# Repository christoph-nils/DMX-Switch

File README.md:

# DMX-Switch

[Hier ist das Projekt inklusive Bilder](http://christoph-nils.de/elektronik/dmx-switch/) bzw. [hier](http://data.christoph-nils.de/diverses/DMX-Switch.zip)  
Ein simpler DMX-Switch für die Hutschiene. Zur Adressierung wird ein Taster gedrückt und speichert die erste Adresse mit DMX-Wert > 128 als Startadresse.  
Ein Kanal kann auch zur Signalisierung eines gültigen DMX-Signals verwendet werden.  
Der Source-Code basiert auf diesem [Code](https://www.mikrocontroller.net/topic/185804)  
Lizenz: http://creativecommons.org/licenses/by-nc/3.0/de/

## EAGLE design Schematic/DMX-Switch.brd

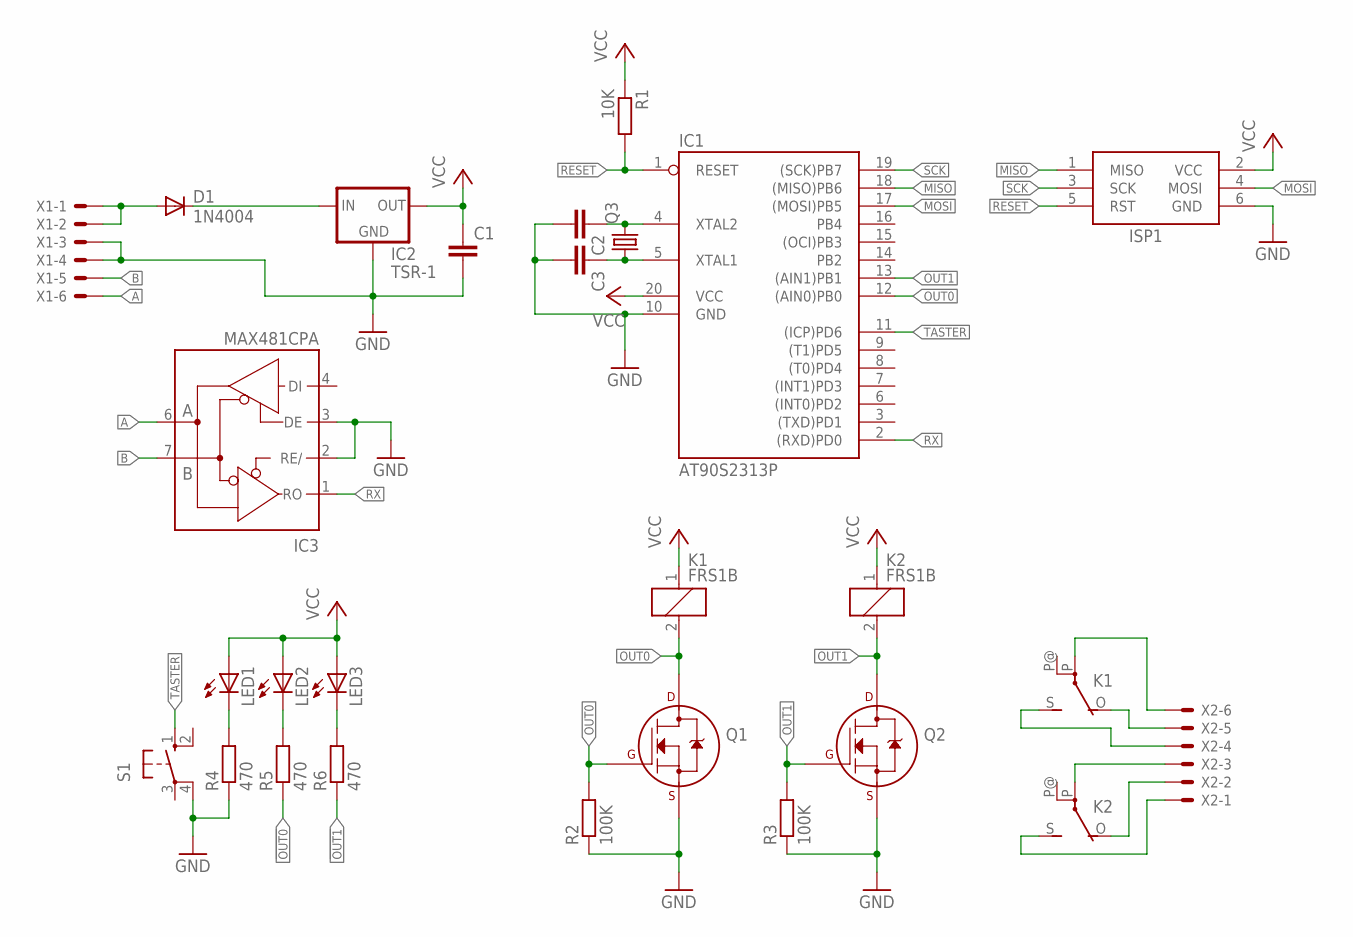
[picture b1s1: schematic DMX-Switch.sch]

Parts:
C1, C2, C3: C-EU025-024X044; C025-024X044
D1: 1N4004; DO41-10
IC1: AT90S2313P; DIL20
IC2: TSR-1
IC3: MAX481CPA; DIL08
ISP1: AVRISP-BOX
K1, K2: FRS1B
LED1, LED2, LED3: LED5MM
Q1, Q2: 2N7000_TO92; TO-92
Q3: CRYSTALHC49S; HC49/S
R1: 10K; 0204/7
R2, R3: 100K; 0204/7
R4, R5, R6: 470; 0204/7
S1: 10-XX; B3F-10XX
X1, X2: KK-156-6

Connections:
!OUT0: K1.2, Q1.3 (D), R5.1
!OUT1: K2.2, Q2.3 (D), R6.1
A: IC3.6 (A), X1.6
B: IC3.7 (B), X1.5
GND: C1.2, C2.2, C3.2, IC1.10 (GND), IC2.2 (GND), IC3.2 (RE/), IC3.3 (DE), IC3.5 (GND), ISP1.6 (GND), Q1.1 (S), Q2.1 (S), R2.1, R3.1, R4.1, S1.4 (P1), X1.3, X1.4
MISO: IC1.18 ((MISO)PB6), ISP1.1 (MISO)
MOSI: IC1.17 ((MOSI)PB5), ISP1.4 (MOSI)
unnamed: D1.A, X1.1, X1.2
unnamed: D1.C, IC2.1 (IN)
unnamed: C3.1, IC1.5 (XTAL1), Q3.1
unnamed: C2.1, IC1.4 (XTAL2), Q3.2
unnamed: LED1.K (C), R4.2
unnamed: LED2.K (C), R5.2
unnamed: LED3.K (C), R6.2
unnamed: K1.S, X2.4
unnamed: K1.O, X2.5
unnamed: K1.P, X2.6
unnamed: K2.P, X2.3
unnamed: K2.O, X2.2
unnamed: K2.S, X2.1
OUT0: IC1.12 ((AIN0)PB0), Q1.2 (G), R2.2
OUT1: IC1.13 ((AIN1)PB1), Q2.2 (G), R3.2
RESET: IC1.1 (RESET), ISP1.5 (RST), R1.2
RX: IC1.2 ((RXD)PD0), IC3.1 (RO)
SCK: IC1.19 ((SCK)PB7), ISP1.3 (SCK)
TASTER: IC1.11 ((ICP)PD6), S1.1 (S)
VCC: C1.1, IC1.20 (VCC), IC2.3 (OUT), IC3.8 (VCC), ISP1.2 (VCC), K1.1, K2.1, LED1.A, LED2.A, LED3.A, R1.1

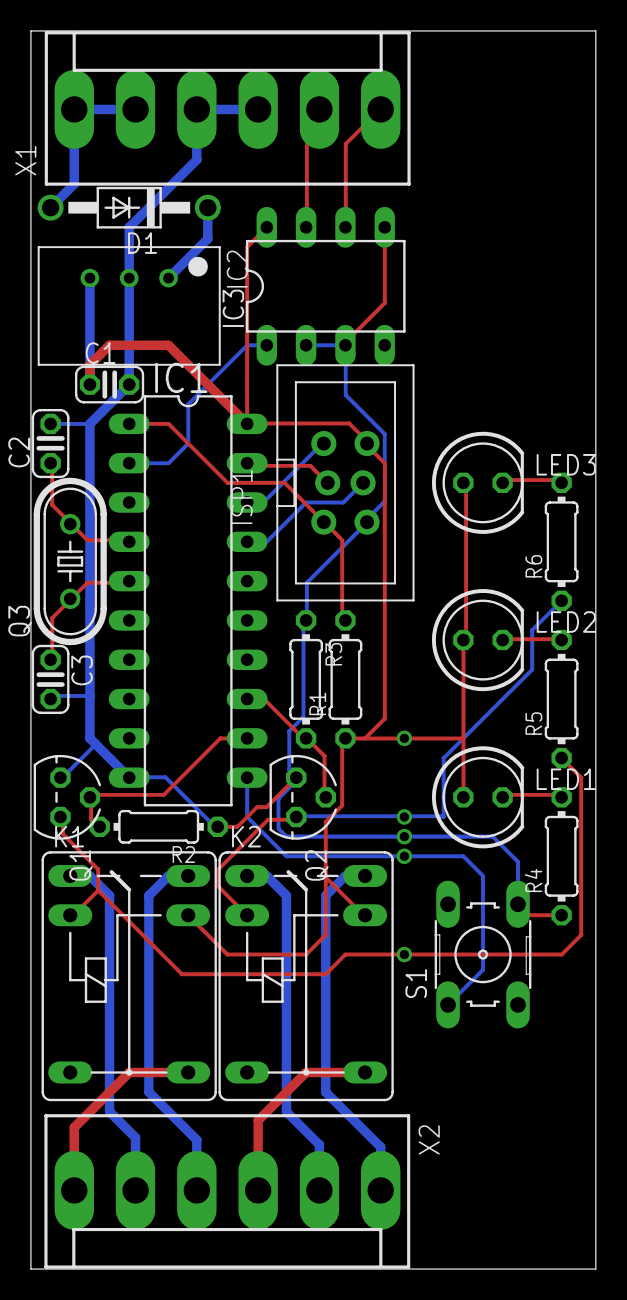
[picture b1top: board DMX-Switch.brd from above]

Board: 2 copper layers, 36.5 x 80.0 mm, 25 parts (0 on the bottom side), 27 nets.

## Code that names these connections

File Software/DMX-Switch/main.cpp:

/**

 * Original https://www.mikrocontroller.net/topic/185804
 * Editiert von Christoph Nils Schäfer <mail@christoph-nils.de>
 * DMX Switch zur Signalisierung der DMX Verfügbarkeit
 * und ein per DMX schaltbarer Kanal
 * Startadresse per Taster und DMX einstellbar

 * DMX Receiver 
 * 2*8bit linear pwm, 2*16bit exponential pwm
 *
 * @author Andi Dittrich <andi.dittrich@a3non.org>
 * @website http://www.a3non.org
 * @modified 31.07.2010
 * @license CC BY-NC
 * @license http://creativecommons.org/licenses/by-nc/3.0/de/
 * @target AtTiny2313
 * @cpu 16MHz
*/
#define F_CPU 16000000UL

#include <avr/interrupt.h>
#include <stdio.h>
#include <inttypes.h>
#include <avr/io.h>
#include <avr/pgmspace.h>
#include <avr/wdt.h>
#include <util/delay.h>
#include <avr/eeprom.h>
#include "mydefs.h"

// number of receiving channels
#define DMX_CHANNELS 1

//PD0	RX
//PD6	Taster Set-CH-n
//PB0	Relais DMX-OK
//PB1	Relais DMX-CH-n

#define	RX_PORT			SBIT( PORTD, 0 )
#define	RX_DDR			SBIT( DDRD,  0 )
#define	Taster_PORT		SBIT( PORTD, 6 )
#define	Taster_PIN		SBIT( PIND,  6 )
#define	Taster_DDR		SBIT( DDRD,  6 )
#define	Relais_0_OUT	SBIT( PORTB, 0 )
#define	Relais_0_DDR	SBIT( DDRB,  0 )
#define	Relais_1_OUT	SBIT( PORTB, 1 )
#define	Relais_1_DDR	SBIT( DDRB,  1 )

// DMX address
volatile uint16_t DMXAddress = 1;

// dmx storage array
volatile uint8_t dmx_data[DMX_CHANNELS];

// dmx states
enum {IDLE = 0, BREAK, READ, SETADDRESS};

// actual dmx state
volatile uint8_t DMXState = IDLE;

// valid sequence
volatile uint8_t VALID_DATA = 0;

// channel input read count
volatile uint16_t DMXFrameCount = 0;


// MAIN
int main(){
	// disable ISR
	cli();
	
	RX_DDR = 0;
	RX_PORT = 0;
	Taster_DDR = 0;
	Taster_PORT = 1;
	Relais_0_OUT = 0;
	Relais_0_DDR = 1;
	Relais_1_OUT = 0;
	Relais_1_DDR = 1;

	// 250k baud - 16MHz - U2X=0
	UBRRL = 3;
	UBRRH = 0;
	
	
	// UART CONTROL
	// 7:0 - RXC - USART Receive Complete
	// 6:0 - TXC - USART Transmit Complete
	// 5:0 - UDRE - USART Data Register Empty
	// 4:0 - FE - Frame Error
	// 3:0 - DOR - Data OverRun
	// 2:0 - UPE - USART Parity Error
	// 1:0 - U2X - Double the USART Transmission Speed
	// 0:0 - MPCM - Multi-processor Communication Mode
	UCSRA = 0b00000000;
	
	// 7:0 - reserved
	// 6:0 - UMSEL - async operation
	// 5:0 - UPM1 - no paritiy
	// 4:0 - UPM0 - no paritiy
	// 3:1 - USBS - 2 stop bits
	// 2:1 - UCSZ1 - 8bit mode
	// 1:1 - UCSZ0 - 8bit mode
	// 0:0 - UCPOL - clock polarity, rising edge
	UCSRC = 0b00001110;

	// UART CONTROL
	// 7:1 - RXCIE - RX Complete Interrupt Enable
	// 6:0 - TXCIE - TX Complete Interrupt Disable
	// 5:0 - UDRIE - USART Data Register Empty Interrupt Disable
	// 4:1 - RXEN - Receiver Enable
	// 3:0 - TXEN - Transmitter Disable
	// 2:0 - UCSZ2 - 8bit mode
	// 1:0 - RXB8 - Receive Data Bit 8
	// 0:0 - TXB8 - Transmit Data Bit 8
	UCSRB = 0b10010000;

	// WATCHDOG - 4s
	// 7:0 - Watchdog Interrupt Flag
	// 6:1 - Watchdog Interrupt Enable
	// 5:1 - Watchdog Timer Prescaler3
	// 4:1 - Watchdog Change Enable
	// 3:0 - Watchdog System Reset Disable
	// 2:0 - Watchdog Timer Prescaler2
	// 1:0 - Watchdog Timer Prescaler1
	// 0:0 - Watchdog Timer Prescaler0
	WDTCR = 0b01110000;	

	// reset watchdog
	MCUSR &= ~(1<<WDRF);
			
	// initialize DMX State
	DMXState = IDLE;

	// initialize data array
	for (uint8_t i=0;i<DMX_CHANNELS;i++){
		dmx_data[i]= 0;
	}

	//Load DMX Address
	DMXAddress = eeprom_read_word(0);

	// enable dmx rx
	sei();

	// main loop
	while (true){
		// assign channels
		if (VALID_DATA){
			// on valid frame, assign values to ouputs
			
			if(dmx_data[0]>=128)
				Relais_1_OUT = 1;
			else
				Relais_1_OUT = 0;
			Relais_0_OUT = 1; //DMX OK
		}else{
			// deactivate all outputs on dmx-line error
			
			Relais_1_OUT = 0;	
			Relais_0_OUT = 0; //DMX not OK
		}

	}

	return 1;
};


/**
 *	ISR SECTION
 */
// DMX RECEIVE
ISR (USART_RX_vect){
	// store ucsra register for frame error flag
	uint8_t statusreg = UCSRA;

	// get data
	uint8_t DMXDataByte = UDR;

	// check for break (error flag is set)
	if (bit_is_set(statusreg, FE)){
		// reset frame counter
		DMXFrameCount = 0;

		// set break status
		DMXState = BREAK;
	
		// abort on frame error
		return;
	}

	// state machine	
	switch (DMXState){
		case BREAK:
			// check for valid startbyte
			DMXState = (DMXDataByte == 0) ? READ : IDLE;
			if(DMXState==READ&&Taster_PIN==0) DMXState = SETADDRESS;
			break;

		case IDLE:
			// do nothing -> wait for break
			break;

		case READ:
			// increment frame count
			DMXFrameCount++;				
			
			// wait for dmx address
			if (DMXFrameCount>=DMXAddress){
				// store value in array
				dmx_data[DMXFrameCount-DMXAddress] = DMXDataByte;
			}
				
			// wait for end of reading channels
			if (DMXFrameCount >= DMXAddress+DMX_CHANNELS-1){
				// activate PWM/Ouput updates
				VALID_DATA = 1;
					
				// set status idle => no action
				DMXState = IDLE;
					
				// reset watchdog
				wdt_reset();
			}			

			break;
		case SETADDRESS:
			// increment frame count
			DMXFrameCount++;
			if(DMXDataByte>=128)
			{
				//Save DMX Address
				eeprom_write_word(0, DMXFrameCount);
				DMXAddress = DMXFrameCount;
				// reset watchdog
				wdt_reset();
				Relais_1_OUT = 0;
				_delay_ms(200);
				Relais_1_OUT = 1;
				_delay_ms(200);
				Relais_1_OUT = 0;
				_delay_ms(200);
				Relais_1_OUT = 1;
				_delay_ms(200);
				Relais_1_OUT = 0;
			}

			if(DMXFrameCount >= 512)
			// set status idle => no action
			DMXState = IDLE;

			// reset watchdog
			wdt_reset();
			break;
	}
}

// Watchdog ISR
ISR(WDT_OVERFLOW_vect){
	// deactivate outputs
	VALID_DATA = 0;
}

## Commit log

2017-09-14 Update README.md
    Zweiter Link zur Projektdatei falls der Server mal wieder down ist.
